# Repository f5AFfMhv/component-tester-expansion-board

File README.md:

# Electronic component tester expansion board

This is PCB expansion board for one of many variants of cheap electronic component testers (see picture).
<br>
[Schematic Rev A](https://github.com/f5AFfMhv/component-tester-expansion-board/raw/master/Rev%20A/component_tester_adapter.pdf)
<br>
[Schematic Rev B](https://github.com/f5AFfMhv/component-tester-expansion-board/raw/master/Rev%20B/schematic.pdf)
<br>
[BOM Rev B](https://raw.githubusercontent.com/f5AFfMhv/component-tester-expansion-board/master/Rev%20B/component_tester_adapter.csv)

## Features

<ul>
  <li>LiPO battery replaces 9V battery.</li>
  <li>1 cell LiPO charger with microUSB connector.</li>
  <li>Adjustable low battery voltage indicator.</li>
</ul>

## Rev B

<ul>
  <li>Removed direct power passthrough from microUSB to MCU over ICSP connector (don't work as expected).</li>
  <li>Changed low battery voltage indicator voltage set resistors values.</li>
  <li>Changed some silkscreen text and position.</li>
</ul>

## Board pictures

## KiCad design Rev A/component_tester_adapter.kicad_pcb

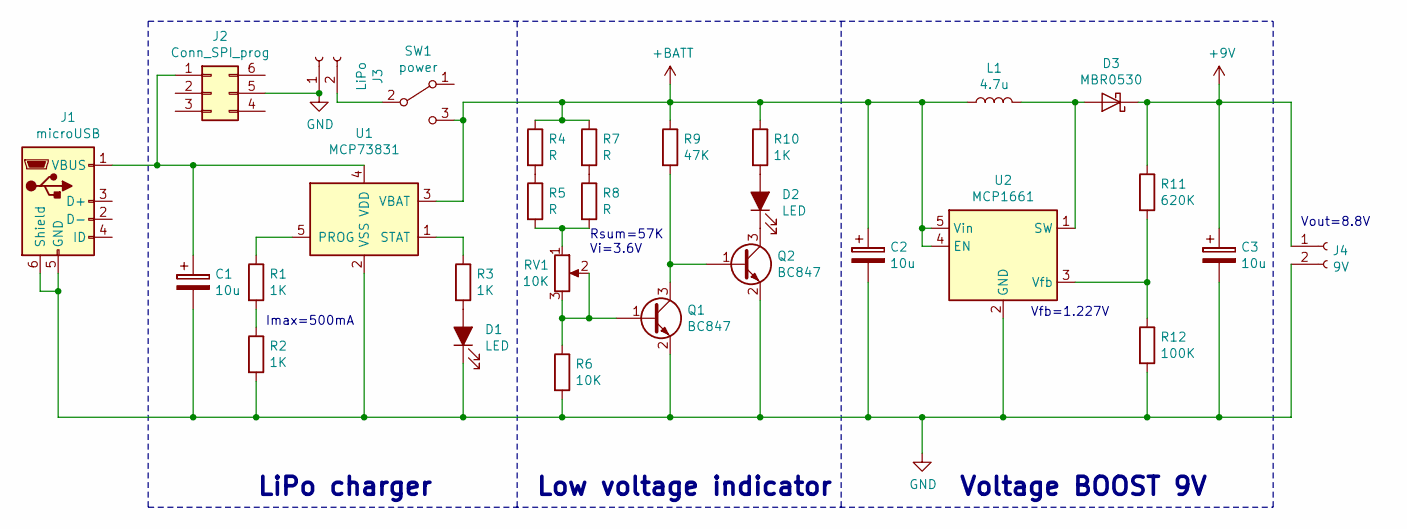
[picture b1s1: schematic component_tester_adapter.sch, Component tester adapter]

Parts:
C1, C2, C3: 10u; C_1206_3216Metric_Pad1.42x1.75mm_HandSolder
D1, D2: LED; LED_0805_2012Metric
D3: MBR0530; D_SOD-123
J1: microUSB; USB_Micro-B_Molex_47346-0001
J2: Conn_SPI_prog; PinHeader_2x03_P2.54mm_Vertical
J3: LiPo; PinHeader_1x02_P2.54mm_Vertical
J4: 9V; PinHeader_1x02_P2.54mm_Vertical
L1: 4.7u; L_0805_2012Metric
Q1, Q2: BC847; SOT-23
R1, R2, R3, R10: 1K; R_0805_2012Metric
R4, R5, R7, R8: R; R_0805_2012Metric
R6: 10K; R_0805_2012Metric
R9: 47K; R_0805_2012Metric
R11: 620K; R_0805_2012Metric
R12: 100K; R_0805_2012Metric
RV1: 10K; Potentiometer_Bourns_3214J_Horizontal
SW1: power; PinHeader_1x03_P2.54mm_Vertical
U1: MCP73831; SOT-23-5
U2: MCP1661; SOT-23-5

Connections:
+9V: C3.1, D3.1 (K), J4.1, R11.1
+BATT: C2.1, L1.1, R4.1, R7.1, R9.1, R10.1, SW1.3 (C), U1.3 (VBAT), U2.4 (EN), U2.5 (Vin)
GND: C1.2, C2.2, C3.2, D1.1 (K), J1.5 (GND), J1.6 (Shield), J2.5, J3.1, J4.2, Q1.2 (E), Q2.2 (E), R2.2, R6.2, R12.2, U1.2 (VSS), U2.2 (GND)
unnamed: C1.1, J1.1 (VBUS), J2.1, U1.4 (VDD)
unnamed: D1.2 (A), R3.2
unnamed: D2.1 (K), Q2.3 (C)
unnamed: D2.2 (A), R10.2
unnamed: D3.2 (A), L1.2, U2.1 (SW)
unnamed: J3.2, SW1.2 (B)
unnamed: Q1.1 (B), R6.1, RV1.2, RV1.3
unnamed: Q1.3 (C), Q2.1 (B), R9.2
unnamed: R1.1, U1.5 (PROG)
unnamed: R1.2, R2.1
unnamed: R3.1, U1.1 (STAT)
unnamed: R4.2, R5.1
unnamed: R5.2, R8.2, RV1.1
unnamed: R7.2, R8.1
unnamed: R11.2, R12.1, U2.3 (Vfb)

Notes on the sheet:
Low voltage indicator
Voltage BOOST 9V
LiPo charger
Imax=500mA
Rsum=57K Vi=3.6V
Vfb=1.227V
Vout=8.8V

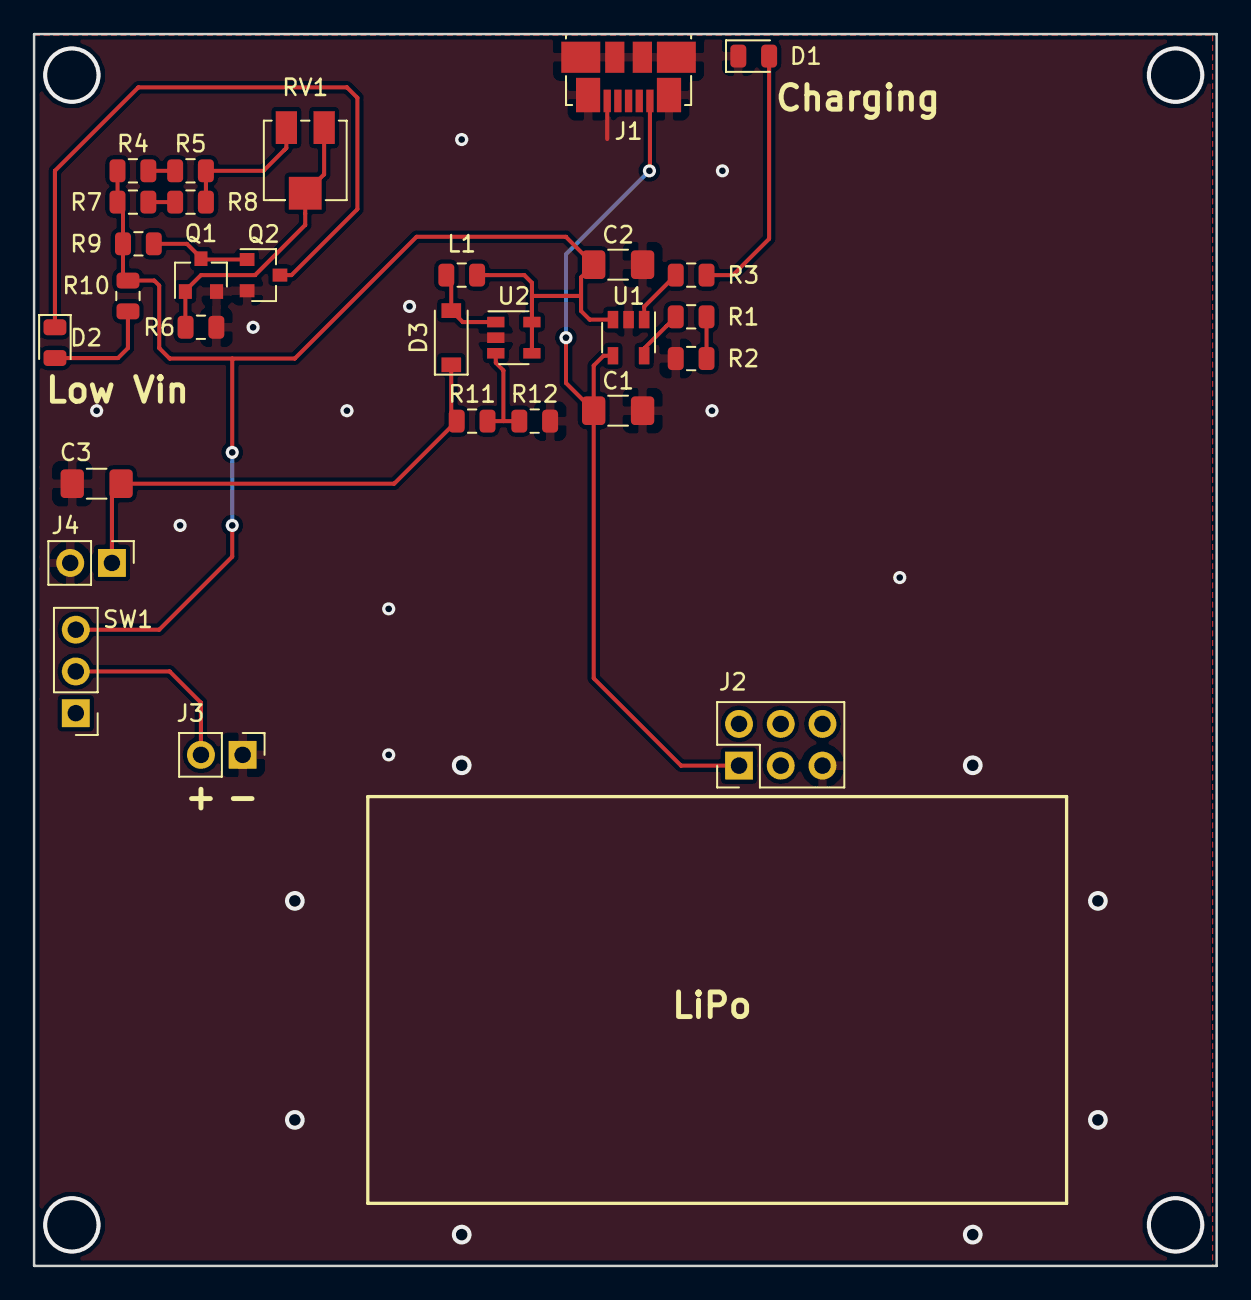
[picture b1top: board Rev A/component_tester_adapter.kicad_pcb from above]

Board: 2 copper layers, 72.0 x 75.0 mm, 29 parts (0 on the bottom side), 18 nets.

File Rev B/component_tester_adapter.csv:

Title,Component tester adapter
Revision,B
Date,2019-02-02
Generated,2019 m. vasario 03 d. 17:08:40
Company,Martynas J.
Comment 1,
Comment 2,
Comment 3,
Comment 4,
Total Parts,27
Total Unique Parts,18



Ref,Qty,Value,Footprint,Datasheet,
C1 C2 C3 ,3,10u,Capacitor_SMD:C_1206_3216Metric_Pad1.42x1.75mm_HandSolder,~
D1 D2 ,2,LED,LED_SMD:LED_0805_2012Metric,~
D3 ,1,MBR0530,Diode_SMD:D_SOD-123,http://www.mccsemi.com/up_pdf/MBR0520~MBR0580(SOD123).pdf
J1 ,1,microUSB,Connector_USB:USB_Micro-B_Molex_47346-0001,~
J2 ,1,LiPo,Connector_PinHeader_2.54mm:PinHeader_1x02_P2.54mm_Vertical,~
J3 ,1,9V,Connector_PinHeader_2.54mm:PinHeader_1x02_P2.54mm_Vertical,~
L1 ,1,4.7u,Inductor_SMD:L_0805_2012Metric,~
Q1 Q2 ,2,BC847,Package_TO_SOT_SMD:SOT-23,http://www.infineon.com/dgdl/Infineon-BC847SERIES_BC848SERIE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
R1 R2 R3 R9 ,4,1K,Resistor_SMD:R_0805_2012Metric,~
R4 ,1,33K,Resistor_SMD:R_0805_2012Metric,~
R5 R6 R7 ,3,10K,Resistor_SMD:R_0805_2012Metric,~
R8 ,1,47K,Resistor_SMD:R_0805_2012Metric,~
R10 ,1,620K,Resistor_SMD:R_0805_2012Metric,~
R11 ,1,100K,Resistor_SMD:R_0805_2012Metric,~
RV1 ,1,10K,Potentiometer_SMD:Potentiometer_Bourns_3214J_Horizontal,~
SW1 ,1,power,Connector_PinHeader_2.54mm:PinHeader_1x03_P2.54mm_Vertical,
U1 ,1,MCP73831,Package_TO_SOT_SMD:SOT-23-5,http://ww1.microchip.com/downloads/en/DeviceDoc/20001984g.pdf
U2 ,1,MCP1661,Package_TO_SOT_SMD:SOT-23-5,http://ww1.microchip.com/downloads/en/DeviceDoc/20005315B.pdf




BOM made with KICAD_BOM_WIZARD (https://github.com/HashDefineElectronics/KiCad_BOM_Wizard.git)
Generated 2019 m. vasario 03 d. 17:08:40

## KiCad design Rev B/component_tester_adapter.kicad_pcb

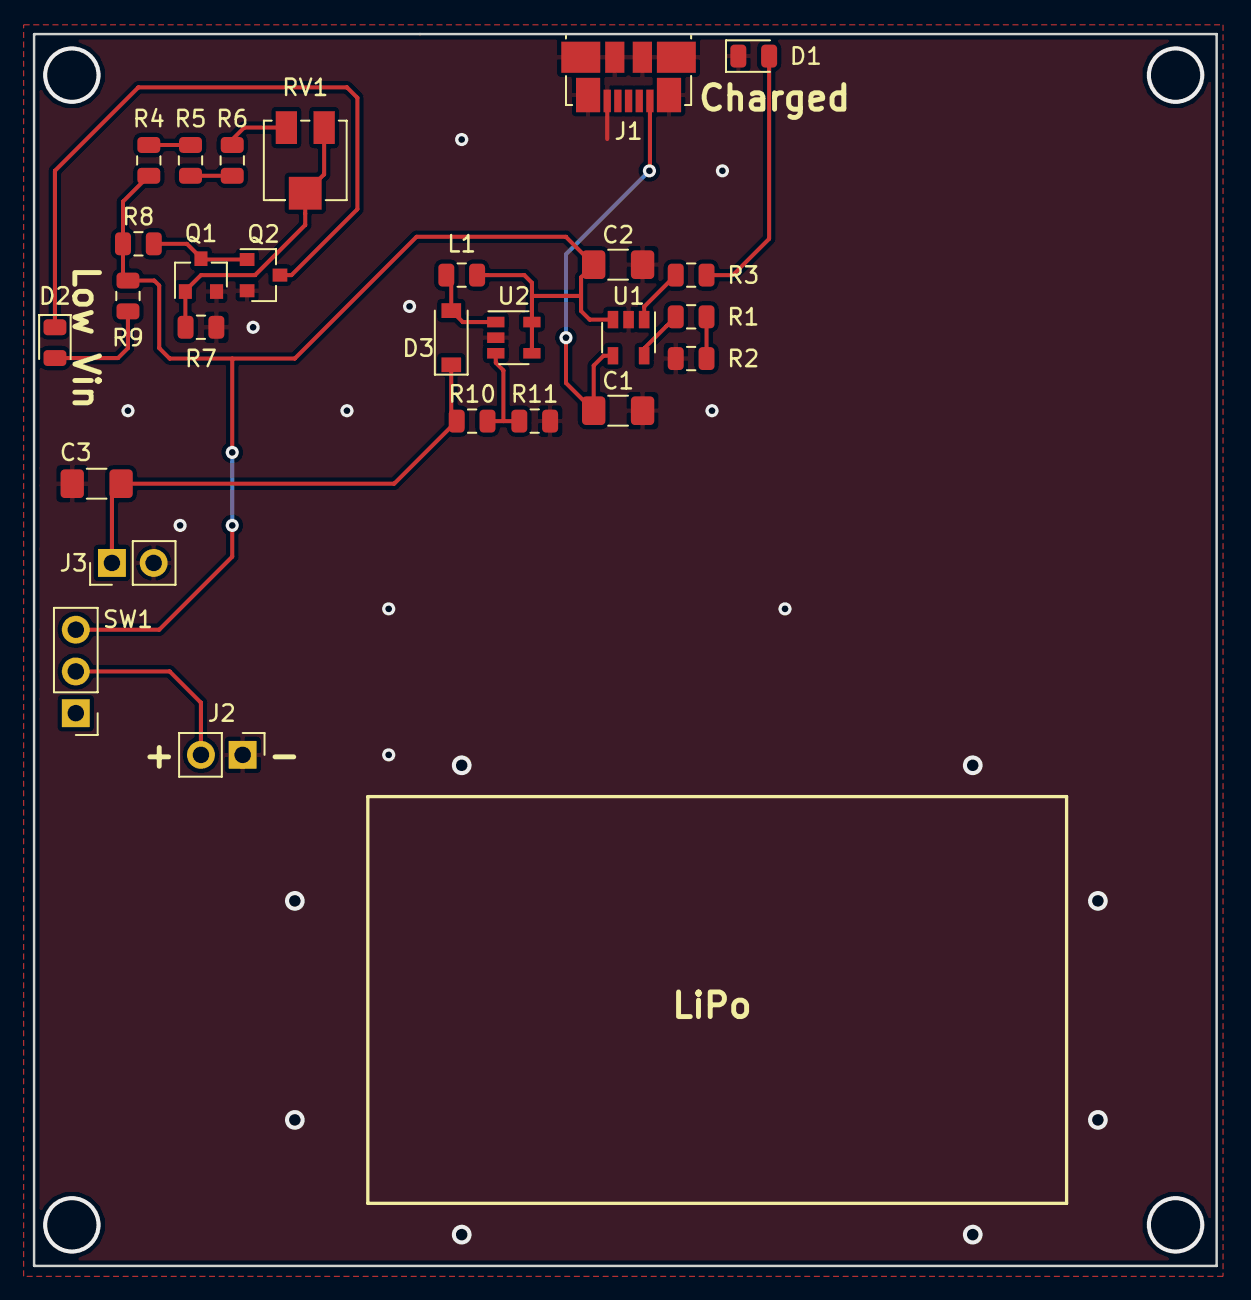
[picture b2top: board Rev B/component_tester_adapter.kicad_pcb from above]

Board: 2 copper layers, 72.0 x 75.0 mm, 27 parts (0 on the bottom side), 18 nets.

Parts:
C1, C2, C3: 10u; C_1206_3216Metric_Pad1.42x1.75mm_HandSolder
D1, D2: LED; LED_0805_2012Metric
D3: MBR0530; D_SOD-123
J1: microUSB; USB_Micro-B_Molex_47346-0001
J2: LiPo; PinHeader_1x02_P2.54mm_Vertical
J3: 9V; PinHeader_1x02_P2.54mm_Vertical
L1: 4.7u; L_0805_2012Metric
Q1, Q2: BC847; SOT-23
R1, R2, R3, R9: 1K; R_0805_2012Metric
R4: 33K; R_0805_2012Metric
R5, R6, R7: 10K; R_0805_2012Metric
R8: 47K; R_0805_2012Metric
R10: 620K; R_0805_2012Metric
R11: 100K; R_0805_2012Metric
RV1: 10K; Potentiometer_Bourns_3214J_Horizontal
SW1: power; PinHeader_1x03_P2.54mm_Vertical
U1: MCP73831; SOT-23-5
U2: MCP1661; SOT-23-5

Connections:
+9V: C3.1, D3.1, J3.1, R10.1
+BATT: C2.1, L1.1, R4.1, R8.1, R9.1, SW1.3, U1.3, U2.4, U2.5
GND: C1.2, C2.2, C3.2, D1.1, J1.5, J1.6, J2.1, J3.2, Q1.2, Q2.2, R2.2, R7.2, R11.2, U1.2, U2.2
unnamed: C1.1, J1.1, U1.4
unnamed: D1.2, R3.2
unnamed: D2.1, Q2.3
unnamed: D2.2, R9.2
unnamed: D3.2, L1.2, U2.1
unnamed: J2.2, SW1.2
unnamed: Q1.1, R7.1, RV1.2, RV1.3
unnamed: Q1.3, Q2.1, R8.2
unnamed: R1.1, U1.5
unnamed: R1.2, R2.1
unnamed: R3.1, U1.1
unnamed: R4.2, R5.1
unnamed: R5.2, R6.1
unnamed: R6.2, RV1.1
unnamed: R10.2, R11.1, U2.3

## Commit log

2019-02-02 added license
2019-02-03 added REV B
2019-02-03 added BOM
